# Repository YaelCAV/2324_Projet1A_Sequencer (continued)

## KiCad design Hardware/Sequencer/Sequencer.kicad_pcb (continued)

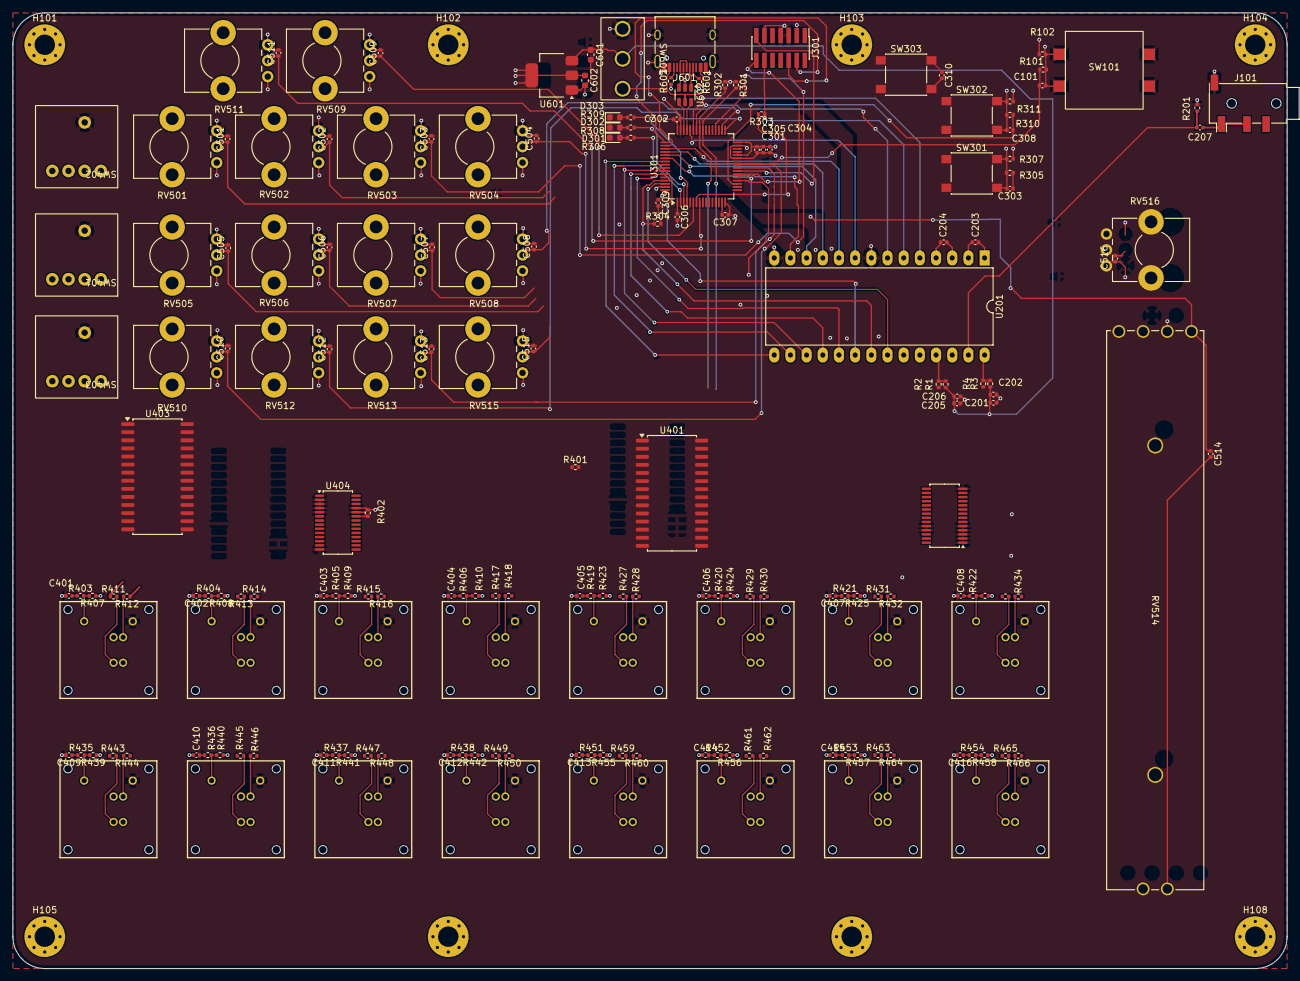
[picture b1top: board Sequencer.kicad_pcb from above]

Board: 4 copper layers, 200.0 x 150.0 mm, 200 parts (0 on the bottom side), 181 nets.

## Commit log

2024-02-29 Create README.md
    needs further completion
2024-02-29 Create Libs
2024-02-29 création de dossiers
2024-02-29 modifs cahier des charges
2024-03-05 Ajouté(e) Diagramme d'architecture.drawio
2024-03-05 Mettre à jour Diagramme d'architecture.drawio
2024-03-05 Mettre à jour Diagramme d'architecture.drawio v1.1
2024-03-05 Mettre à jour Diagramme d'architecture.drawio v1.2
2024-03-07 Ajouté(e) Diagramme d'architecture vfinal.drawio
2024-03-07 Mettre à jour Diagramme d'architecture vfinal.drawio
2024-03-14 update schematic
2024-03-14 test
2024-03-14 ADC connexion
2024-03-14 GPIO
2024-03-14 Régu
2024-03-14 project add
2024-03-14 dossiers retouchés
2024-03-28 Beaucoup de changements sur le pcb
    Alim corrigée, ajout de l'USB C
    Sonde sur le processeur + linkage USB
    Rajout des boutons (465M111...)
2024-03-28 pcb créé pour les estimations des dimensions de la carte
2024-03-28 actualisation pcb de test
2024-03-30 update dimension pcb, footprint
2024-04-01 much changes everywhere
2024-04-04 Create journal_de_bord.md
    création journal de bord
2024-04-04 PCB PCB
2024-04-04 SCHEMA CORRECTION LED
2024-04-04 schematics
2024-04-04 update pcb
2024-04-04 PCB PCB PCB
2024-04-04 PCB uP bientot fini
2024-04-04 PCB TERMINE (sauf erreurs bizarres et optimisation)
2024-04-05 finalize pcb
2024-04-25 maj du readme
2024-04-25 MAJ readme
2024-04-25 Design du socle 3D
2024-04-25 ajout de 2 formats 3D pour le design du boitier
2024-05-02 Ajout diagramme fonctionnement code Sequencer
2024-05-02 changement impression 3D
2024-05-16 plans 3D
2024-05-28 maj Livrables et 3D
2024-05-28 ajout livrables
2024-05-29 ajout fichier problemes.md
2024-05-29 ajout manuel d'utilisation
2024-06-06 màj readme
